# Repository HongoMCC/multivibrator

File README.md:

# multivibrator

astable multivibrator soldering practice kit

## bill of materials
- D1, D2: LED
- R1, R2: 330Ω
- R3, R4: 10kΩ
- C1, C2: 100uF
- Q1, Q2: 2SC1815
- J1: [XH Connector](https://akizukidenshi.com/catalog/g/g112247/)
- JP1: Jumper Wire

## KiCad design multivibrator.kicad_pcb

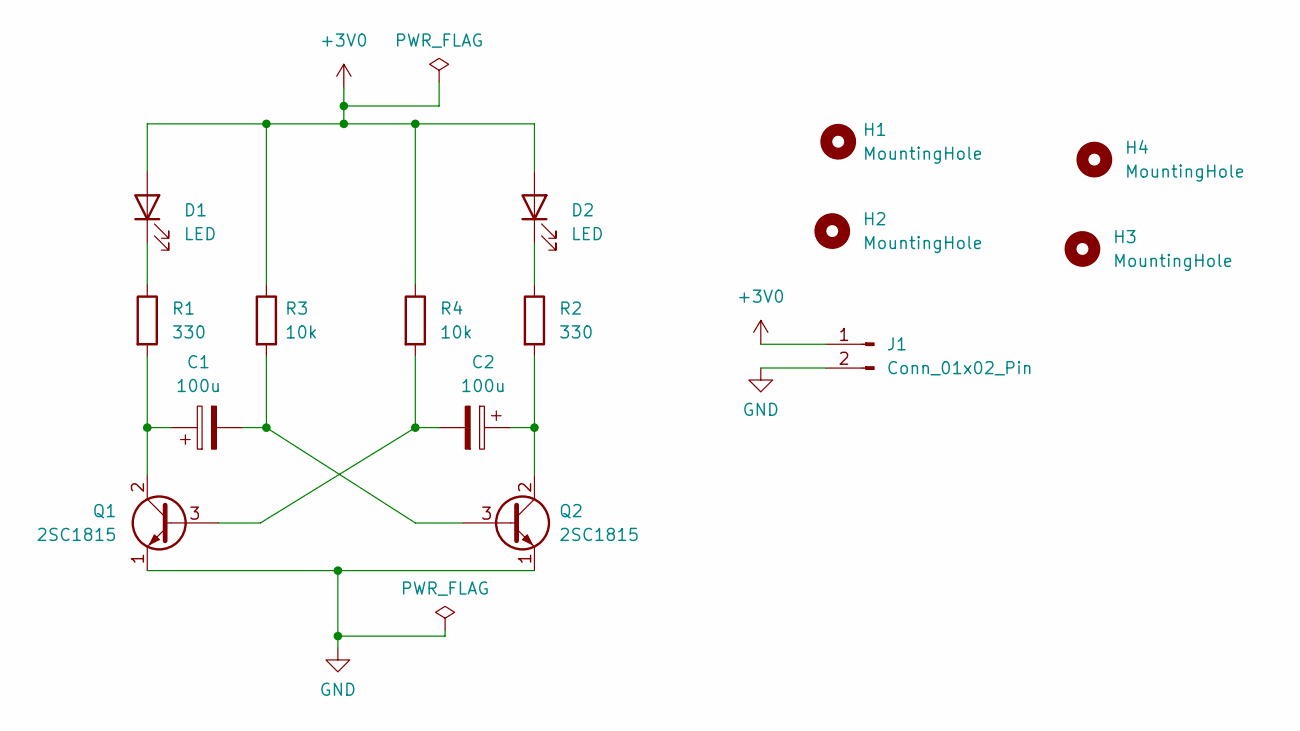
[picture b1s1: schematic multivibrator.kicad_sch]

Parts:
C1, C2: 100u; CP_Radial_D5.0mm_P2.50mm
D1, D2: LED; LED_D5.0mm
H1, H2, H3, H4: MountingHole; MountingHole_3.2mm_M3
J1: Conn_01x02_Pin; JST_XH_B2B-XH-A_1x02_P2.50mm_Vertical
Q1, Q2: 2SC1815; TO-92L_Inline_Wide
R1, R2: 330; R_Axial_DIN0207_L6.3mm_D2.5mm_P10.16mm_Horizontal
R3, R4: 10k; R_Axial_DIN0207_L6.3mm_D2.5mm_P10.16mm_Horizontal

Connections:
+3V0: D1.2 (A), D2.2 (A), J1.1, R3.1, R4.1
GND: J1.2, Q1.1 (E), Q2.1 (E)
unnamed: D1.1 (K), R1.1
unnamed: D2.1 (K), R2.1
unnamed: C2.2, Q1.3 (B), R4.2
unnamed: C1.1, Q1.2 (C), R1.2
unnamed: C1.2, Q2.3 (B), R3.2
unnamed: C2.1, Q2.2 (C), R2.2

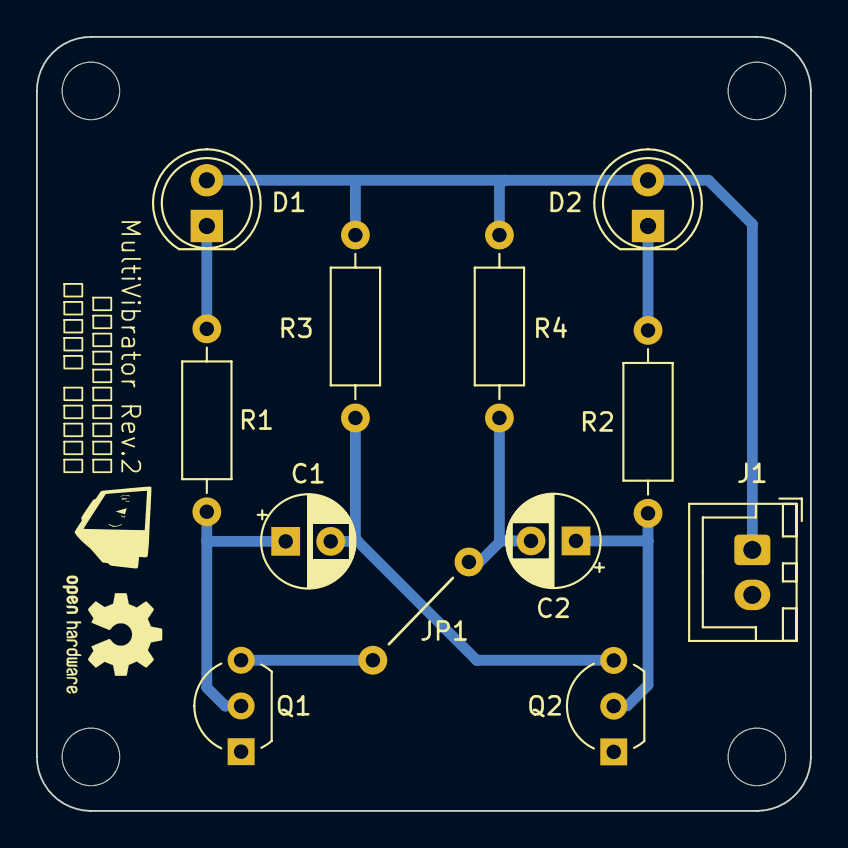
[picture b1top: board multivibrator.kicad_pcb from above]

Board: 2 copper layers, 43.0 x 43.0 mm, 15 parts (0 on the bottom side), 8 nets.

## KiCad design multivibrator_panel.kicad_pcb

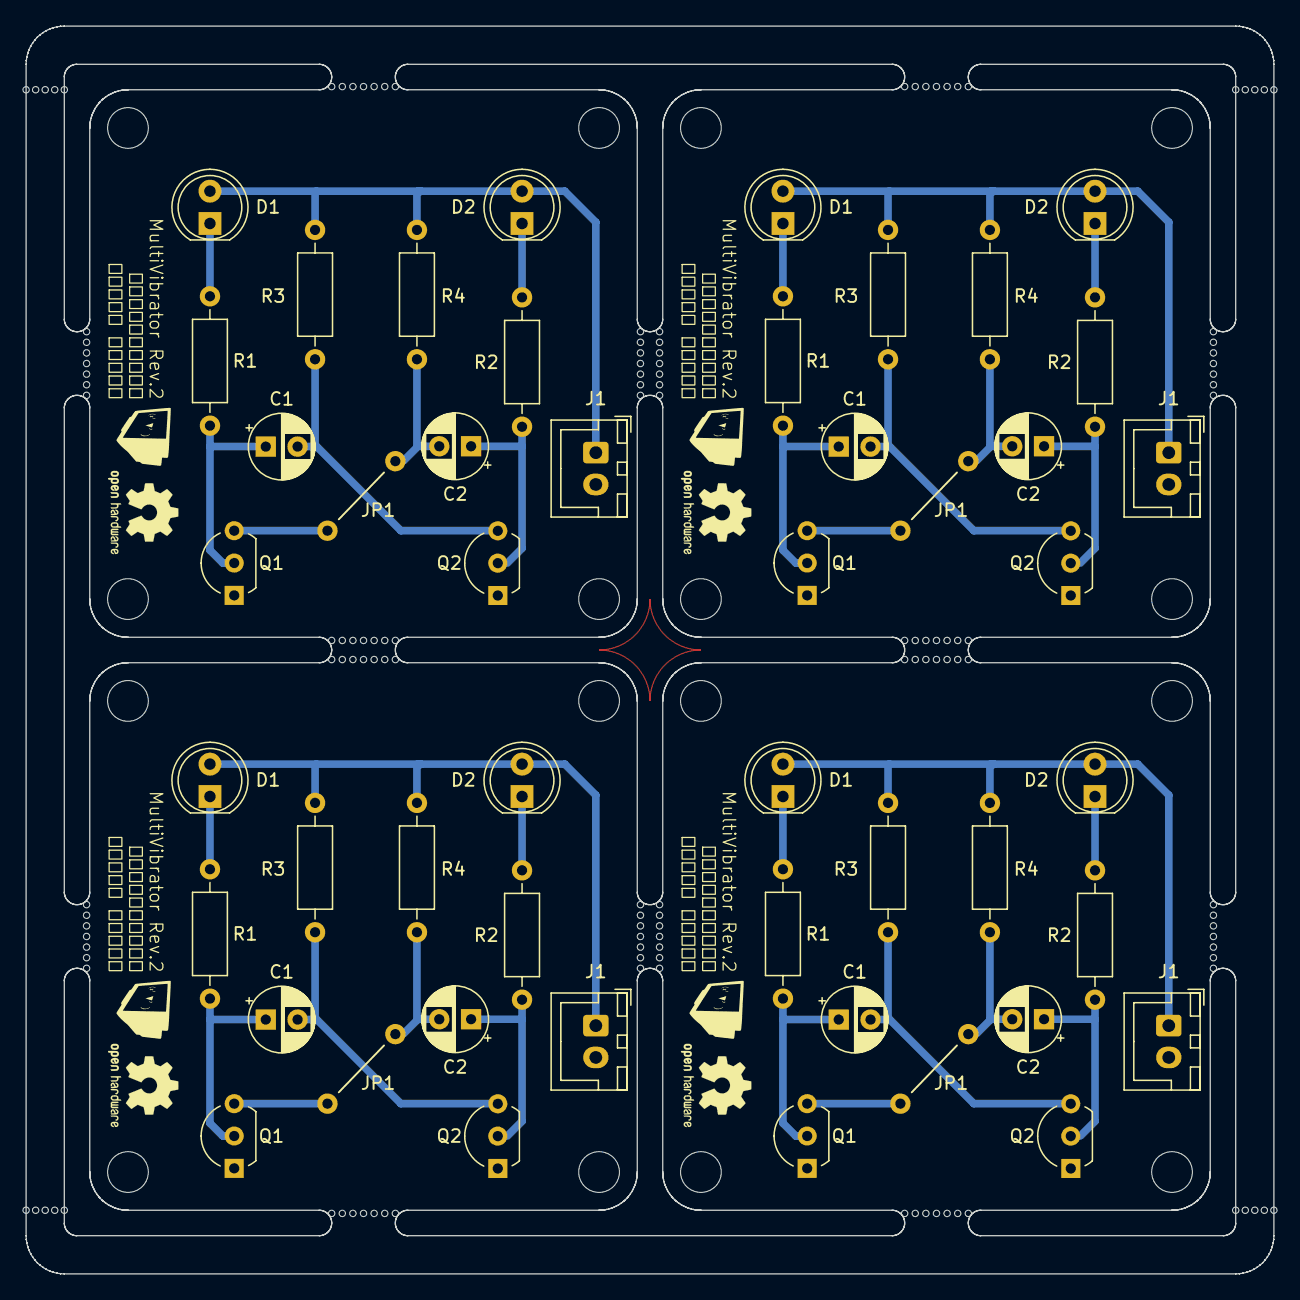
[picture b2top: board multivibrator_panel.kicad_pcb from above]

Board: 2 copper layers, 98.0 x 98.0 mm, 192 parts (0 on the bottom side), 32 nets.

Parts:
C1, C1#2, C1#3, C1#4, C2, C2#2, C2#3, C2#4: 100u; CP_Radial_D5.0mm_P2.50mm
D1, D1#2, D1#3, D1#4, D2, D2#2, D2#3, D2#4: LED; LED_D5.0mm
H1, H1#2, H1#3, H1#4, H2, H2#2, H2#3, H2#4, H3, H3#2, H3#3, H3#4, H4, H4#2, H4#3, H4#4: MountingHole; MountingHole_3.2mm_M3
J1, J1#2, J1#3, J1#4: Conn_01x02_Pin; JST_XH_B2B-XH-A_1x02_P2.50mm_Vertical
KiKit_MB_1_1, KiKit_MB_1_2, KiKit_MB_1_3, KiKit_MB_1_4, KiKit_MB_1_5, KiKit_MB_1_6, KiKit_MB_1_7, KiKit_MB_2_1, KiKit_MB_2_2, KiKit_MB_2_3, KiKit_MB_2_4, KiKit_MB_2_5, KiKit_MB_2_6, KiKit_MB_2_7, KiKit_MB_3_1, KiKit_MB_3_2, KiKit_MB_3_3, KiKit_MB_3_4, KiKit_MB_3_5, KiKit_MB_3_6, KiKit_MB_3_7, KiKit_MB_4_1, KiKit_MB_4_2, KiKit_MB_4_3, KiKit_MB_4_4, KiKit_MB_4_5, KiKit_MB_4_6, KiKit_MB_4_7, KiKit_MB_5_1, KiKit_MB_5_2, KiKit_MB_5_3, KiKit_MB_5_4, KiKit_MB_5_5, KiKit_MB_5_6, KiKit_MB_5_7, KiKit_MB_6_1, KiKit_MB_6_2, KiKit_MB_6_3, KiKit_MB_6_4, KiKit_MB_6_5, KiKit_MB_6_6, KiKit_MB_6_7, KiKit_MB_7_1, KiKit_MB_7_2, KiKit_MB_7_3, KiKit_MB_7_4, KiKit_MB_7_5, KiKit_MB_7_6, KiKit_MB_7_7, KiKit_MB_8_1, KiKit_MB_8_2, KiKit_MB_8_3, KiKit_MB_8_4, KiKit_MB_8_5, KiKit_MB_8_6, KiKit_MB_8_7, KiKit_MB_9_1, KiKit_MB_9_2, KiKit_MB_9_3, KiKit_MB_9_4, KiKit_MB_9_5, KiKit_MB_9_6, KiKit_MB_9_7, KiKit_MB_10_1, KiKit_MB_10_2, KiKit_MB_10_3, KiKit_MB_10_4, KiKit_MB_10_5, KiKit_MB_10_6, KiKit_MB_10_7, KiKit_MB_11_1, KiKit_MB_11_2, KiKit_MB_11_3, KiKit_MB_11_4, KiKit_MB_11_5, KiKit_MB_11_6, KiKit_MB_11_7, KiKit_MB_12_1, KiKit_MB_12_2, KiKit_MB_12_3, KiKit_MB_12_4, KiKit_MB_12_5, KiKit_MB_12_6, KiKit_MB_12_7, KiKit_MB_13_1, KiKit_MB_13_2, KiKit_MB_13_3, KiKit_MB_13_4, KiKit_MB_13_5, KiKit_MB_13_6, KiKit_MB_13_7, KiKit_MB_14_1, KiKit_MB_14_2, KiKit_MB_14_3, KiKit_MB_14_4, KiKit_MB_14_5, KiKit_MB_14_6, KiKit_MB_14_7, KiKit_MB_15_1, KiKit_MB_15_2, KiKit_MB_15_3, KiKit_MB_15_4, KiKit_MB_15_5, KiKit_MB_15_6, KiKit_MB_15_7, KiKit_MB_16_1, KiKit_MB_16_2, KiKit_MB_16_3, KiKit_MB_16_4, KiKit_MB_16_5, KiKit_MB_16_6, KiKit_MB_16_7, KiKit_MB_17_1, KiKit_MB_17_2, KiKit_MB_17_3, KiKit_MB_17_4, KiKit_MB_17_5, KiKit_MB_18_1, KiKit_MB_18_2, KiKit_MB_18_3, KiKit_MB_18_4, KiKit_MB_18_5, KiKit_MB_19_1, KiKit_MB_19_2, KiKit_MB_19_3, KiKit_MB_19_4, KiKit_MB_19_5, KiKit_MB_20_1, KiKit_MB_20_2, KiKit_MB_20_3, KiKit_MB_20_4, KiKit_MB_20_5: NPTH
Q1, Q1#2, Q1#3, Q1#4, Q2, Q2#2, Q2#3, Q2#4: 2SC1815; TO-92L_Inline_Wide
R1, R1#2, R1#3, R1#4, R2, R2#2, R2#3, R2#4: 330; R_Axial_DIN0207_L6.3mm_D2.5mm_P10.16mm_Horizontal
R3, R3#2, R3#3, R3#4, R4, R4#2, R4#3, R4#4: 10k; R_Axial_DIN0207_L6.3mm_D2.5mm_P10.16mm_Horizontal

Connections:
Board_0-+3V0: D1.2 (A), D2#4.2 (A), J1#3.1, R3#3.1, R4#3.1
Board_0-GND: J1#3.2, Q1#4.1 (E), Q2.1 (E)
Board_0-Net-(D1-K): D1.1 (K), R1#3.1
Board_0-Net-(D2-K): D2#4.1 (K), R2#4.1
Board_0-Net-(Q1-B): C2.2, Q1#4.3 (B), R4#3.2
Board_0-Net-(Q1-C): C1.1, Q1#4.2 (C), R1#3.2
Board_0-Net-(Q2-B): C1.2, Q2.3 (B), R3#3.2
Board_0-Net-(Q2-C): C2.1, Q2.2 (C), R2#4.2
Board_1-+3V0: D1#4.2 (A), D2#3.2 (A), J1#2.1, R3.1, R4#4.1
Board_1-GND: J1#2.2, Q1#3.1 (E), Q2#4.1 (E)
Board_1-Net-(D1-K): D1#4.1 (K), R1#4.1
Board_1-Net-(D2-K): D2#3.1 (K), R2.1
Board_1-Net-(Q1-B): C2#4.2, Q1#3.3 (B), R4#4.2
Board_1-Net-(Q1-C): C1#3.1, Q1#3.2 (C), R1#4.2
Board_1-Net-(Q2-B): C1#3.2, Q2#4.3 (B), R3.2
Board_1-Net-(Q2-C): C2#4.1, Q2#4.2 (C), R2.2
Board_2-+3V0: D1#2.2 (A), D2#2.2 (A), J1#4.1, R3#4.1, R4.1
Board_2-GND: J1#4.2, Q1#2.1 (E), Q2#3.1 (E)
Board_2-Net-(D1-K): D1#2.1 (K), R1#2.1
Board_2-Net-(D2-K): D2#2.1 (K), R2#3.1
Board_2-Net-(Q1-B): C2#2.2, Q1#2.3 (B), R4.2
Board_2-Net-(Q1-C): C1#4.1, Q1#2.2 (C), R1#2.2
Board_2-Net-(Q2-B): C1#4.2, Q2#3.3 (B), R3#4.2
Board_2-Net-(Q2-C): C2#2.1, Q2#3.2 (C), R2#3.2
Board_3-+3V0: D1#3.2 (A), D2.2 (A), J1.1, R3#2.1, R4#2.1
Board_3-GND: J1.2, Q1.1 (E), Q2#2.1 (E)
Board_3-Net-(D1-K): D1#3.1 (K), R1.1
Board_3-Net-(D2-K): D2.1 (K), R2#2.1
Board_3-Net-(Q1-B): C2#3.2, Q1.3 (B), R4#2.2
Board_3-Net-(Q1-C): C1#2.1, Q1.2 (C), R1.2
Board_3-Net-(Q2-B): C1#2.2, Q2#2.3 (B), R3#2.2
Board_3-Net-(Q2-C): C2#3.1, Q2#2.2 (C), R2#2.2

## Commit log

2024-06-30 init
2024-06-30 up to date
2024-06-30 feat: replace footprints of capacitors and connector
2024-06-30 chore: panelize
2024-06-30 chore: delete panel.kicad_pro
2024-06-30 doc: Update README.md
2024-08-26 feat: widen jump wire
2024-08-26 chore: panelize and generate gerber
2024-08-27 fix: resolve weird path and regenerate gerber
